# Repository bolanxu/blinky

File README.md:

# Blinky

A small figdet project I made 7th grade year as a birthday gift for a friend.

A very small and simple toy that repeats the pattern of tones and lights that you input into it. At the core is an 8-pin microcontroller called the STC15W204S, which
is part of the 8051 microcontroller family developed by Intel in the 80's. But a company named STC Microcontrollers decided to continue development on it with
added features such as ADC, more timers, PWM, SPI, and others. This was the first microcontroller I learned (I should have learned Arduino first) and one of the first
projects I made with it.

I don't have an image of it sadly because the only prototype I built I gave to my friend. When I get a chance, I will try to get one. But here is a look at the schematic
and pcb designs designed in Autodesk EAGLE.

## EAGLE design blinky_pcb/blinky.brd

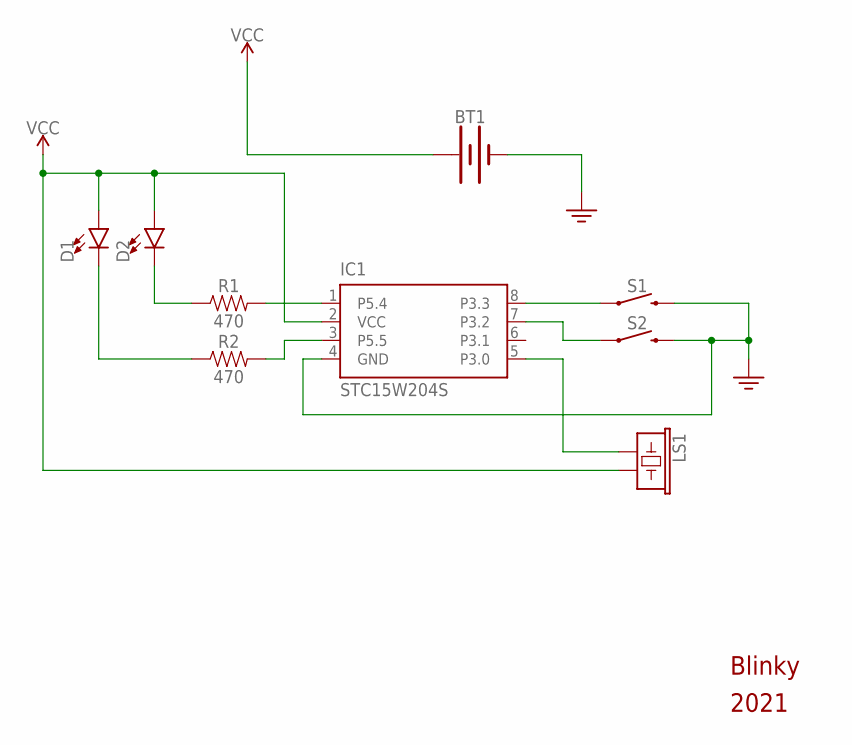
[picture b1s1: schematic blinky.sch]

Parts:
BT1: BATTERY-20MM_PTH; BATTCOM_20MM_PTH
D1, D2: LED5MM; LED_5MM
IC1: STC15W204S; SOP-08
LS1: BUZZER-PTH; BUZZER-12MM
R1, R2: 470; AXIAL-0.3
S1, S2: MOMENTARY-SWITCH-SPST-PTH-6.0MM; TACTILE_SWITCH_PTH_6.0MM

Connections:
GND: BT1.2 (-), IC1.4 (GND), S1.3 (2), S2.3 (2)
unnamed: D2.K (C), R1.P$1 (1)
unnamed: D1.K (C), R2.P$1 (1)
unnamed: IC1.1 (P5.4), R1.P$2 (2)
unnamed: IC1.3 (P5.5), R2.P$2 (2)
unnamed: IC1.8 (P3.3), S1.1
unnamed: IC1.7 (P3.2), S2.1
unnamed: IC1.5 (P3.0), LS1.+ (1)
VCC: BT1.1 (+), D1.A, D2.A, IC1.2 (VCC), LS1.- (2)

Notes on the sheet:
Blinky
2021

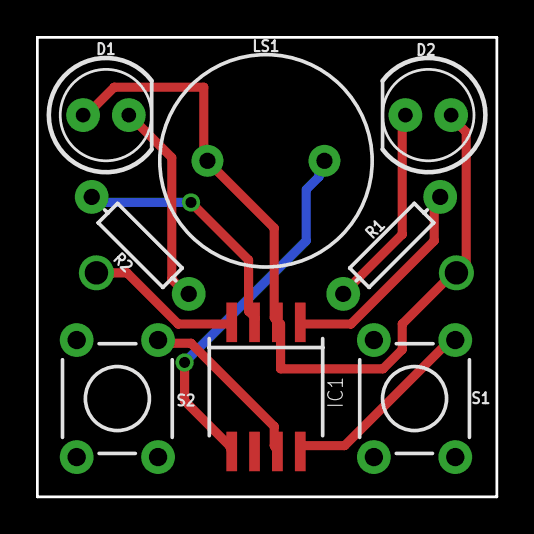
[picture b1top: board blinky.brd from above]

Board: 2 copper layers, 25.5 x 25.5 mm, 9 parts (1 on the bottom side), 9 nets.

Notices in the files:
parts and their libraries:
SparkFun-Switches: Licensing: Creative Commons ShareAlike 4.0 International - https://creativecommons.org/licenses/by-sa/4.0
